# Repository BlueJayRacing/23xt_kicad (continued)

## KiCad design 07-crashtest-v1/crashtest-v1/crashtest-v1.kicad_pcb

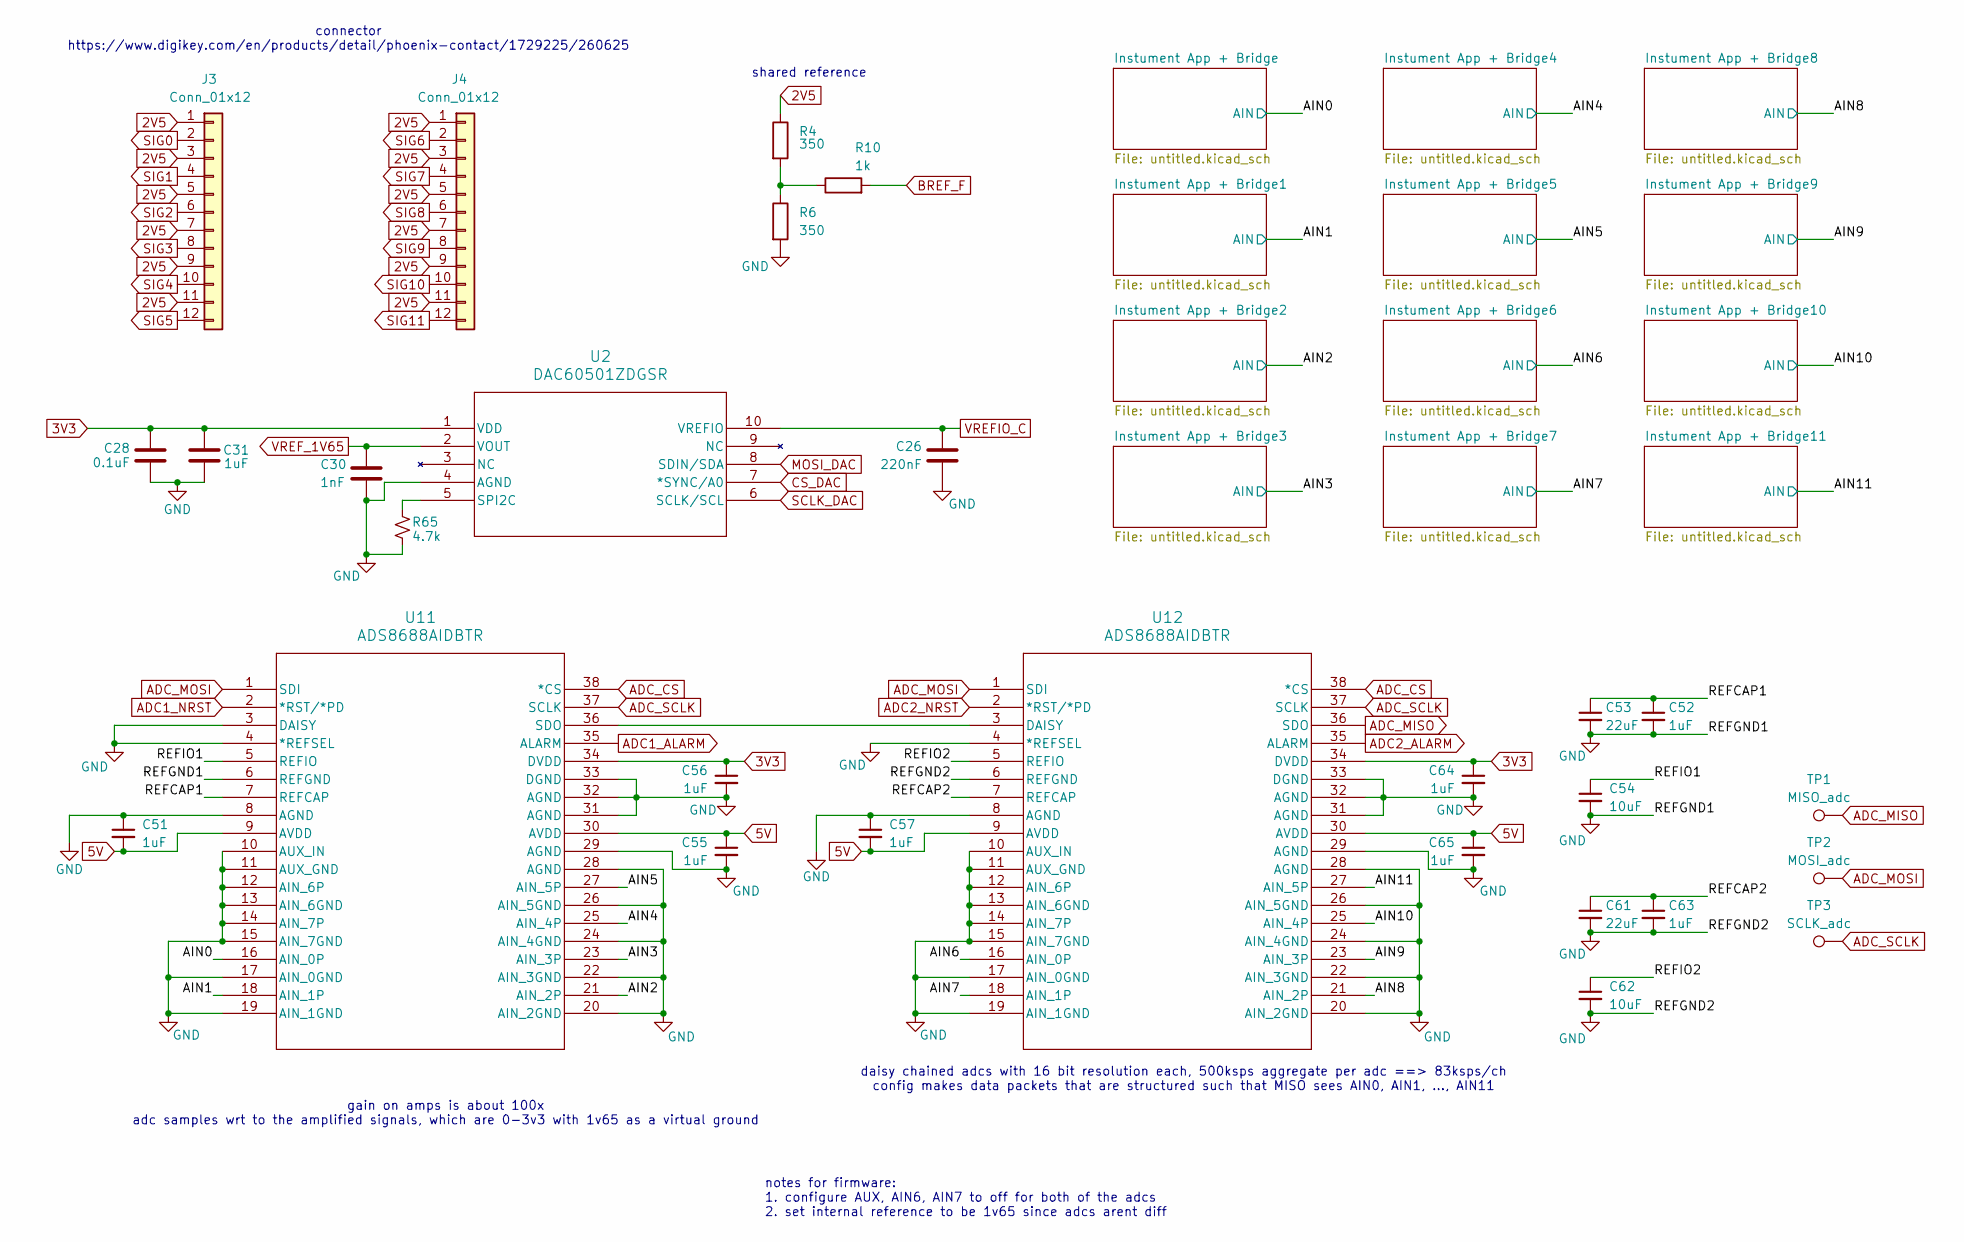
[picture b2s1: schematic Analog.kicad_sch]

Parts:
C26: 220nF; C_0603_1608Metric_Pad1.08x0.95mm_HandSolder
C28: 0.1uF; C_0603_1608Metric_Pad1.08x0.95mm_HandSolder
C30: 1nF; C_0603_1608Metric_Pad1.08x0.95mm_HandSolder
C31, C51, C52, C55, C56, C57, C63, C64, C65: 1uF; C_0603_1608Metric_Pad1.08x0.95mm_HandSolder
C53, C61: 22uF; C_0603_1608Metric_Pad1.08x0.95mm_HandSolder
C54, C62: 10uF; C_0603_1608Metric_Pad1.08x0.95mm_HandSolder
J3, J4: Conn_01x12; TerminalBlock_Phoenix_MKDS-1,5-12-5.08_1x12_P5.08mm_Horizon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
R4, R6: 350; R_0603_1608Metric_Pad0.98x0.95mm_HandSolder
R10: 1k; R_0603_1608Metric_Pad0.98x0.95mm_HandSolder
R65: 4.7k; R_0603_1608Metric_Pad0.98x0.95mm_HandSolder
TP1: MISO_adc; TestPoint_Pad_1.0x1.0mm
TP2: MOSI_adc; TestPoint_Pad_1.0x1.0mm
TP3: SCLK_adc; TestPoint_Pad_1.0x1.0mm
U2: DAC60501ZDGSR; MSOP-10_3x3mm_P0.5mm
U11, U12: ADS8688AIDBTR; DBT38_TEX-L

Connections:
2V5: J3.1, J3.3, J3.5, J3.7, J3.9, J3.11, J4.1, J4.3, J4.5, J4.7, J4.9, J4.11, R4.1; also elsewhere on the board
3V3: C28.1, C31.1, C56.1, C64.1, U2.1 (VDD), U11.34 (DVDD), U12.34 (DVDD); also elsewhere on the board
5V: C51.2, C55.1, C57.2, C65.1, U11.9 (AVDD), U11.30 (AVDD), U12.9 (AVDD), U12.30 (AVDD); also elsewhere on the board
/Analog/AIN0: U11.16 (AIN_0P); also elsewhere on the board
/Analog/AIN1: U11.18 (AIN_1P); also elsewhere on the board
/Analog/AIN2: U11.21 (AIN_2P); also elsewhere on the board
/Analog/AIN3: U11.23 (AIN_3P); also elsewhere on the board
/Analog/AIN4: U11.25 (AIN_4P); also elsewhere on the board
/Analog/AIN5: U11.27 (AIN_5P); also elsewhere on the board
/Analog/AIN6: U12.16 (AIN_0P); also elsewhere on the board
/Analog/AIN7: U12.18 (AIN_1P); also elsewhere on the board
/Analog/AIN8: U12.21 (AIN_2P); also elsewhere on the board
/Analog/AIN9: U12.23 (AIN_3P); also elsewhere on the board
/Analog/AIN10: U12.25 (AIN_4P); also elsewhere on the board
/Analog/AIN11: U12.27 (AIN_5P); also elsewhere on the board
/Analog/REFCAP1: C52.1, C53.1, U11.7 (REFCAP)
/Analog/REFCAP2: C61.1, C63.1, U12.7 (REFCAP)
/Analog/REFIO1: C54.1, U11.5 (REFIO)
/Analog/REFIO2: C62.1, U12.5 (REFIO)
ADC1_ALARM: U11.35 (ALARM); also elsewhere on the board
ADC1_NRST: U11.2 (*RST/*PD); also elsewhere on the board
ADC2_ALARM: U12.35 (ALARM); also elsewhere on the board
ADC2_NRST: U12.2 (*RST/*PD); also elsewhere on the board
ADC_CS: U11.38 (*CS), U12.38 (*CS); also elsewhere on the board
ADC_MISO: TP1.1 (1_1), U12.36 (SDO); also elsewhere on the board
ADC_MOSI: TP2.1 (1_1), U11.1 (SDI), U12.1 (SDI); also elsewhere on the board
ADC_SCLK: TP3.1 (1_1), U11.37 (SCLK), U12.37 (SCLK); also elsewhere on the board
BREF_F: R10.2; also elsewhere on the board
CS_DAC: U2.7 (*SYNC/A0); also elsewhere on the board
GND: C26.1, C28.2, C30.1, C31.2, C51.1, C52.2, C53.2, C54.2, C55.2, C56.2, C57.1, C61.2, C62.2, C63.2, C64.2, C65.2, R6.2, R65.2, U2.4 (AGND), U11.3 (DAISY), U11.4 (*REFSEL), U11.6 (REFGND), U11.8 (AGND), U11.10 (AUX_IN), U11.11 (AUX_GND), U11.12 (AIN_6P), U11.13 (AIN_6GND), U11.14 (AIN_7P), U11.15 (AIN_7GND), U11.17 (AIN_0GND), U11.19 (AIN_1GND), U11.20 (AIN_2GND), U11.22 (AIN_3GND), U11.24 (AIN_4GND), U11.26 (AIN_5GND), U11.28 (AGND), U11.29 (AGND), U11.31 (AGND), U11.32 (AGND), U11.33 (DGND), U12.4 (*REFSEL), U12.6 (REFGND), U12.8 (AGND), U12.10 (AUX_IN), U12.11 (AUX_GND), U12.12 (AIN_6P), U12.13 (AIN_6GND), U12.14 (AIN_7P), U12.15 (AIN_7GND), U12.17 (AIN_0GND), U12.19 (AIN_1GND), U12.20 (AIN_2GND), U12.22 (AIN_3GND), U12.24 (AIN_4GND), U12.26 (AIN_5GND), U12.28 (AGND), U12.29 (AGND), U12.31 (AGND), U12.32 (AGND), U12.33 (DGND); also elsewhere on the board
MOSI_DAC: U2.8 (SDIN/SDA); also elsewhere on the board
unnamed: R4.2, R6.1, R10.1
unnamed: R65.1, U2.5 (SPI2C)
unnamed: U11.36 (SDO), U12.3 (DAISY)
SCLK_DAC: U2.6 (SCLK/SCL); also elsewhere on the board
SIG0: J3.2; also elsewhere on the board
SIG1: J3.4
SIG2: J3.6
SIG3: J3.8
SIG4: J3.10
SIG5: J3.12
SIG6: J4.2
SIG7: J4.4
SIG8: J4.6
SIG9: J4.8
SIG10: J4.10
SIG11: J4.12
VREFIO_C: C26.2, U2.10 (VREFIO)
VREF_1V65: C30.2, U2.2 (VOUT); also elsewhere on the board

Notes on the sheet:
shared reference
connector https://www.digikey.com/en/products/detail/phoenix-contact/1729225/260625
notes for firmware: 1. configure AUX, AIN6, AIN7 to off for both of the adcs 2. set internal reference to be 1v65 since adcs arent diff
gain on amps is about 100x adc samples wrt to the amplified signals, which are 0-3v3 with 1v65 as a virtual ground
daisy chained adcs with 16 bit resolution each, 500ksps aggregate per adc ==> 83ksps/ch config makes data packets that are structured such that MISO sees AIN0, AIN1, ..., AIN11

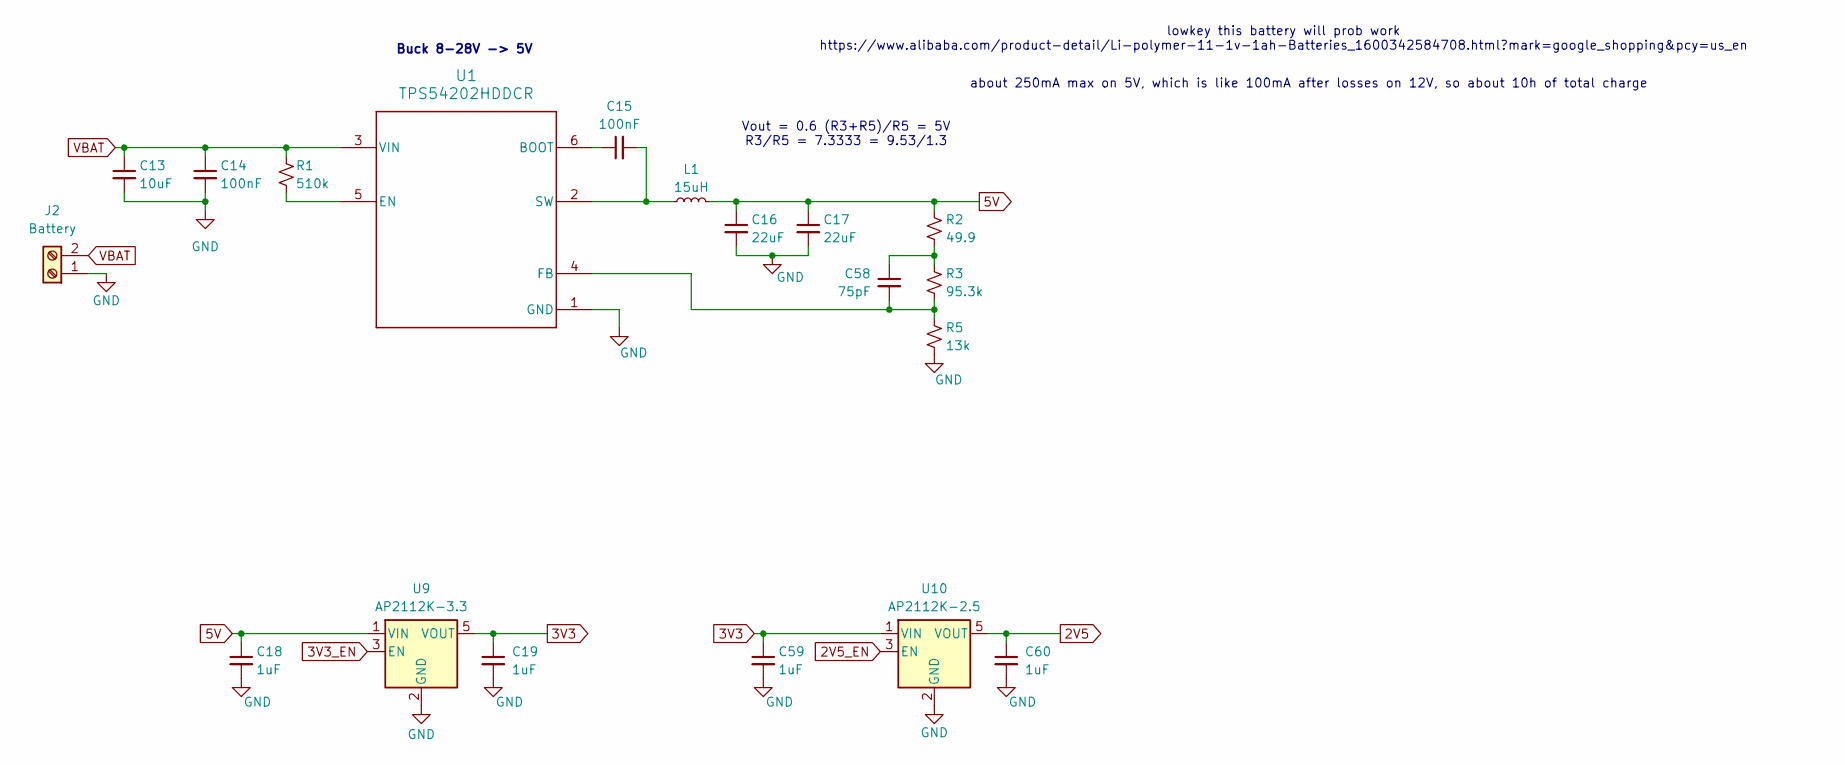
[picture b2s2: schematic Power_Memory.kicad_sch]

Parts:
C13: 10uF; C_0603_1608Metric_Pad1.08x0.95mm_HandSolder
C14, C15: 100nF; C_0603_1608Metric_Pad1.08x0.95mm_HandSolder
C16, C17: 22uF; C_0603_1608Metric_Pad1.08x0.95mm_HandSolder
C18, C19, C59, C60: 1uF; C_0603_1608Metric_Pad1.08x0.95mm_HandSolder
C58: 75pF; C_0603_1608Metric_Pad1.08x0.95mm_HandSolder
J2: Battery; TerminalBlock_Phoenix_MKDS-1,5-2-5.08_1x02_P5.08mm_Horizont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
L1: 15uH; L_0603_1608Metric_Pad1.05x0.95mm_HandSolder
R1: 510k; R_0603_1608Metric_Pad0.98x0.95mm_HandSolder
R2: 49.9; R_0603_1608Metric_Pad0.98x0.95mm_HandSolder
R3: 95.3k; R_0603_1608Metric_Pad0.98x0.95mm_HandSolder
R5: 13k; R_0603_1608Metric_Pad0.98x0.95mm_HandSolder
U1: TPS54202HDDCR; DDC0006A_L
U9: AP2112K-3.3; SOT-23-5
U10: AP2112K-2.5; SOT-23-5

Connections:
2V5: C60.1, U10.5 (VOUT); also elsewhere on the board
2V5_EN: U10.3 (EN); also elsewhere on the board
3V3: C19.1, C59.1, U9.5 (VOUT), U10.1 (VIN); also elsewhere on the board
3V3_EN: U9.3 (EN); also elsewhere on the board
5V: C16.1, C17.1, C18.1, L1.2, R2.1, U9.1 (VIN); also elsewhere on the board
GND: C13.2, C14.2, C16.2, C17.2, C18.2, C19.2, C59.2, C60.2, J2.1, R5.2, U1.1 (GND), U9.2 (GND), U10.2 (GND); also elsewhere on the board
unnamed: C58.1, R2.2, R3.1
unnamed: C15.1, U1.6 (BOOT)
unnamed: R1.2, U1.5 (EN)
unnamed: C58.2, R3.2, R5.1, U1.4 (FB)
unnamed: C15.2, L1.1, U1.2 (SW)
VBAT: C13.1, C14.1, J2.2, R1.1, U1.3 (VIN)

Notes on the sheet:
lowkey this battery will prob work https://www.alibaba.com/product-detail/Li-polymer-11-1v-1ah-Batteries_1600342584708.html?mark=google_shopping&pcy=us_en
about 250mA max on 5V, which is like 100mA after losses on 12V, so about 10h of total charge
Buck 8-28V -> 5V
Vout = 0.6 (R3+R5)/R5 = 5V R3/R5 = 7.3333 = 9.53/1.3

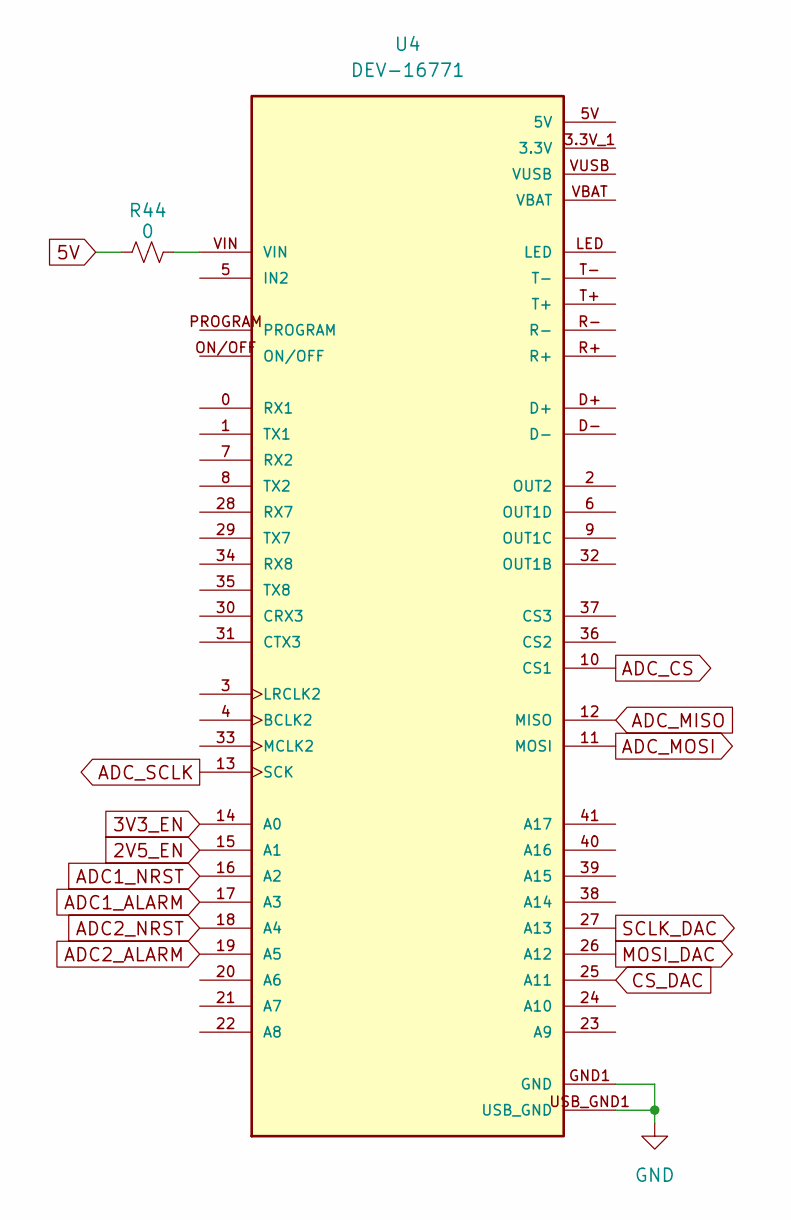
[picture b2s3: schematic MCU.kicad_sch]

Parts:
R44: 0; R_0603_1608Metric_Pad0.98x0.95mm_HandSolder
U4: DEV-16771; MODULE_DEV-16771; PARTREV 4.1

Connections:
2V5_EN: U4.15 (A1); also elsewhere on the board
3.3V: U4.3.3V_1 (3.3V), U4.3.3V_2 (3.3V), U4.3.3V_3 (3.3V)
3V3_EN: U4.14 (A0); also elsewhere on the board
5V: R44.1; also elsewhere on the board
ADC1_ALARM: U4.17 (A3); also elsewhere on the board
ADC1_NRST: U4.16 (A2); also elsewhere on the board
ADC2_ALARM: U4.19 (A5); also elsewhere on the board
ADC2_NRST: U4.18 (A4); also elsewhere on the board
ADC_CS: U4.10 (CS1); also elsewhere on the board
ADC_MISO: U4.12 (MISO); also elsewhere on the board
ADC_MOSI: U4.11 (MOSI); also elsewhere on the board
ADC_SCLK: U4.13 (SCK); also elsewhere on the board
CS_DAC: U4.25 (A11); also elsewhere on the board
GND: U4.GND1 (GND), U4.GND2 (GND), U4.GND3 (GND), U4.GND4 (GND), U4.GND5 (GND), U4.USB_GND1 (USB_GND), U4.USB_GND2 (USB_GND); also elsewhere on the board
MOSI_DAC: U4.26 (A12); also elsewhere on the board
unnamed: R44.2, U4.VIN
SCLK_DAC: U4.27 (A13); also elsewhere on the board

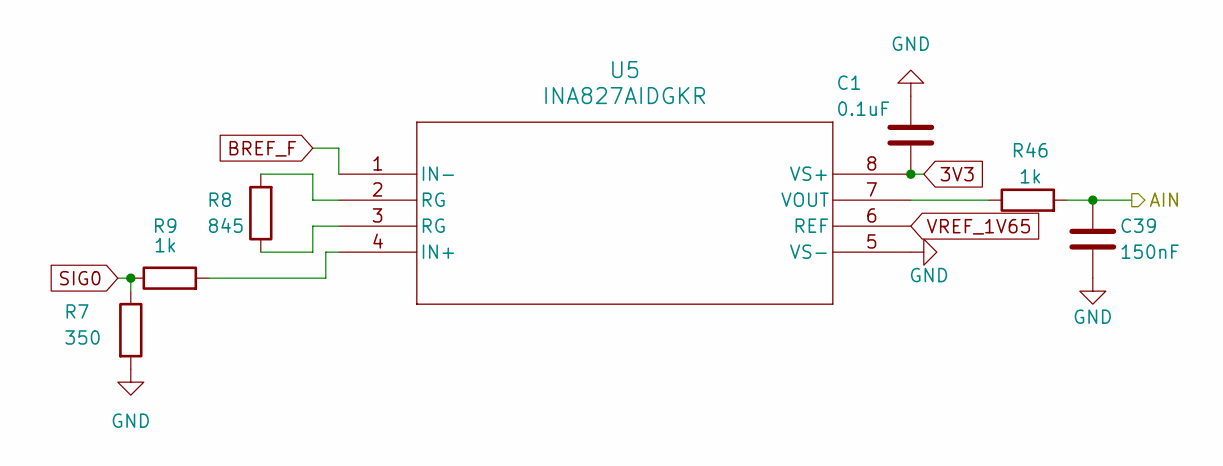
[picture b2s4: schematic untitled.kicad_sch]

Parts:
C1: 0.1uF; C_0603_1608Metric_Pad1.08x0.95mm_HandSolder
C39: 150nF; C_0603_1608Metric_Pad1.08x0.95mm_HandSolder
R7: 350; R_0603_1608Metric_Pad0.98x0.95mm_HandSolder
R8: 845; R_0603_1608Metric_Pad0.98x0.95mm_HandSolder
R9, R46: 1k; R_0603_1608Metric_Pad0.98x0.95mm_HandSolder
U5: INA827AIDGKR; VSSOP-8_3x3mm_P0.65mm

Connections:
3V3: C1.1, U5.8 (VS+); also elsewhere on the board
/Analog/AIN0: C39.2, R46.2; also elsewhere on the board
BREF_F: U5.1 (IN-); also elsewhere on the board
GND: C1.2, C39.1, R7.2, U5.5 (VS-); also elsewhere on the board
unnamed: R8.1, U5.3 (RG)
unnamed: R8.2, U5.2 (RG)
unnamed: R9.2, U5.4 (IN+)
unnamed: R46.1, U5.7 (VOUT)
SIG0: R7.1, R9.1; also elsewhere on the board
VREF_1V65: U5.6 (REF); also elsewhere on the board

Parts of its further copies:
C2, C3, C4, C5, C6, C7, C8, C9, C10, C11, C12: 0.1uF; C_0603_1608Metric_Pad1.08x0.95mm_HandSolder
C40, C41, C42, C43, C44, C45, C46, C47, C48, C49, C50: 150nF; C_0603_1608Metric_Pad1.08x0.95mm_HandSolder
R11, R14, R17, R20, R23, R26, R29, R32, R35, R38, R41: 350; R_0603_1608Metric_Pad0.98x0.95mm_HandSolder
R12, R15, R18, R21, R24, R27, R30, R33, R36, R39, R42, R47, R48, R49, R50, R51, R52, R53, R54, R55, R56, R57: 1k; R_0603_1608Metric_Pad0.98x0.95mm_HandSolder
R13, R16, R19, R22, R25, R28, R31, R34, R37, R40, R43: 845; R_0603_1608Metric_Pad0.98x0.95mm_HandSolder
U6, U7, U8, U14, U15, U16, U17, U18, U19, U20, U21: INA827AIDGKR; VSSOP-8_3x3mm_P0.65mm

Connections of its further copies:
3V3: C2.1, C3.1, C4.1, C5.1, C6.1, C7.1, C8.1, C9.1, C10.1, C11.1, C12.1, U6.8 (VS+), U7.8 (VS+), U8.8 (VS+), U14.8 (VS+), U15.8 (VS+), U16.8 (VS+), U17.8 (VS+), U18.8 (VS+), U19.8 (VS+), U20.8 (VS+), U21.8 (VS+); also elsewhere on the board
/Analog/AIN1: C40.2, R47.2; also elsewhere on the board
/Analog/AIN2: C41.2, R48.2; also elsewhere on the board
/Analog/AIN3: C42.2, R49.2; also elsewhere on the board
/Analog/AIN4: C43.2, R50.2; also elsewhere on the board
/Analog/AIN5: C44.2, R51.2; also elsewhere on the board
/Analog/AIN6: C45.2, R52.2; also elsewhere on the board
/Analog/AIN7: C46.2, R53.2; also elsewhere on the board
/Analog/AIN8: C47.2, R54.2; also elsewhere on the board
/Analog/AIN9: C48.2, R55.2; also elsewhere on the board
/Analog/AIN10: C49.2, R56.2; also elsewhere on the board
/Analog/AIN11: C50.2, R57.2; also elsewhere on the board
BREF_F: U6.1 (IN-), U7.1 (IN-), U8.1 (IN-), U14.1 (IN-), U15.1 (IN-), U16.1 (IN-), U17.1 (IN-), U18.1 (IN-), U19.1 (IN-), U20.1 (IN-), U21.1 (IN-); also elsewhere on the board
GND: C2.2, C3.2, C4.2, C5.2, C6.2, C7.2, C8.2, C9.2, C10.2, C11.2, C12.2, C40.1, C41.1, C42.1, C43.1, C44.1, C45.1, C46.1, C47.1, C48.1, C49.1, C50.1, R11.2, R14.2, R17.2, R20.2, R23.2, R26.2, R29.2, R32.2, R35.2, R38.2, R41.2, U6.5 (VS-), U7.5 (VS-), U8.5 (VS-), U14.5 (VS-), U15.5 (VS-), U16.5 (VS-), U17.5 (VS-), U18.5 (VS-), U19.5 (VS-), U20.5 (VS-), U21.5 (VS-); also elsewhere on the board
unnamed: R13.1, U6.3 (RG)
unnamed: R13.2, U6.2 (RG)
unnamed: R16.1, U7.3 (RG)
unnamed: R16.2, U7.2 (RG)
unnamed: R19.1, U8.3 (RG)
unnamed: R19.2, U8.2 (RG)
unnamed: R22.1, U14.3 (RG)
unnamed: R22.2, U14.2 (RG)
unnamed: R25.1, U15.3 (RG)
unnamed: R25.2, U15.2 (RG)
unnamed: R28.1, U16.3 (RG)
unnamed: R28.2, U16.2 (RG)
unnamed: R31.1, U17.3 (RG)
unnamed: R31.2, U17.2 (RG)
unnamed: R34.1, U18.3 (RG)
unnamed: R34.2, U18.2 (RG)
unnamed: R37.1, U19.3 (RG)
unnamed: R37.2, U19.2 (RG)
unnamed: R40.1, U20.3 (RG)
unnamed: R40.2, U20.2 (RG)
unnamed: R43.1, U21.3 (RG)
unnamed: R43.2, U21.2 (RG)
unnamed: R12.2, U6.4 (IN+)
unnamed: R47.1, U6.7 (VOUT)
unnamed: R15.2, U7.4 (IN+)
unnamed: R48.1, U7.7 (VOUT)
unnamed: R18.2, U8.4 (IN+)
unnamed: R49.1, U8.7 (VOUT)
unnamed: R21.2, U14.4 (IN+)
unnamed: R50.1, U14.7 (VOUT)
unnamed: R24.2, U15.4 (IN+)
unnamed: R51.1, U15.7 (VOUT)
unnamed: R27.2, U16.4 (IN+)
unnamed: R52.1, U16.7 (VOUT)
unnamed: R30.2, U17.4 (IN+)
unnamed: R53.1, U17.7 (VOUT)
unnamed: R33.2, U18.4 (IN+)
unnamed: R54.1, U18.7 (VOUT)
unnamed: R36.2, U19.4 (IN+)
unnamed: R55.1, U19.7 (VOUT)
unnamed: R39.2, U20.4 (IN+)
unnamed: R56.1, U20.7 (VOUT)
unnamed: R42.2, U21.4 (IN+)
unnamed: R57.1, U21.7 (VOUT)
SIG0: R11.1, R12.1, R14.1, R15.1, R17.1, R18.1, R20.1, R21.1, R23.1, R24.1, R26.1, R27.1, R29.1, R30.1, R32.1, R33.1, R35.1, R36.1, R38.1, R39.1, R41.1, R42.1; also elsewhere on the board
VREF_1V65: U6.6 (REF), U7.6 (REF), U8.6 (REF), U14.6 (REF), U15.6 (REF), U16.6 (REF), U17.6 (REF), U18.6 (REF), U19.6 (REF), U20.6 (REF), U21.6 (REF); also elsewhere on the board

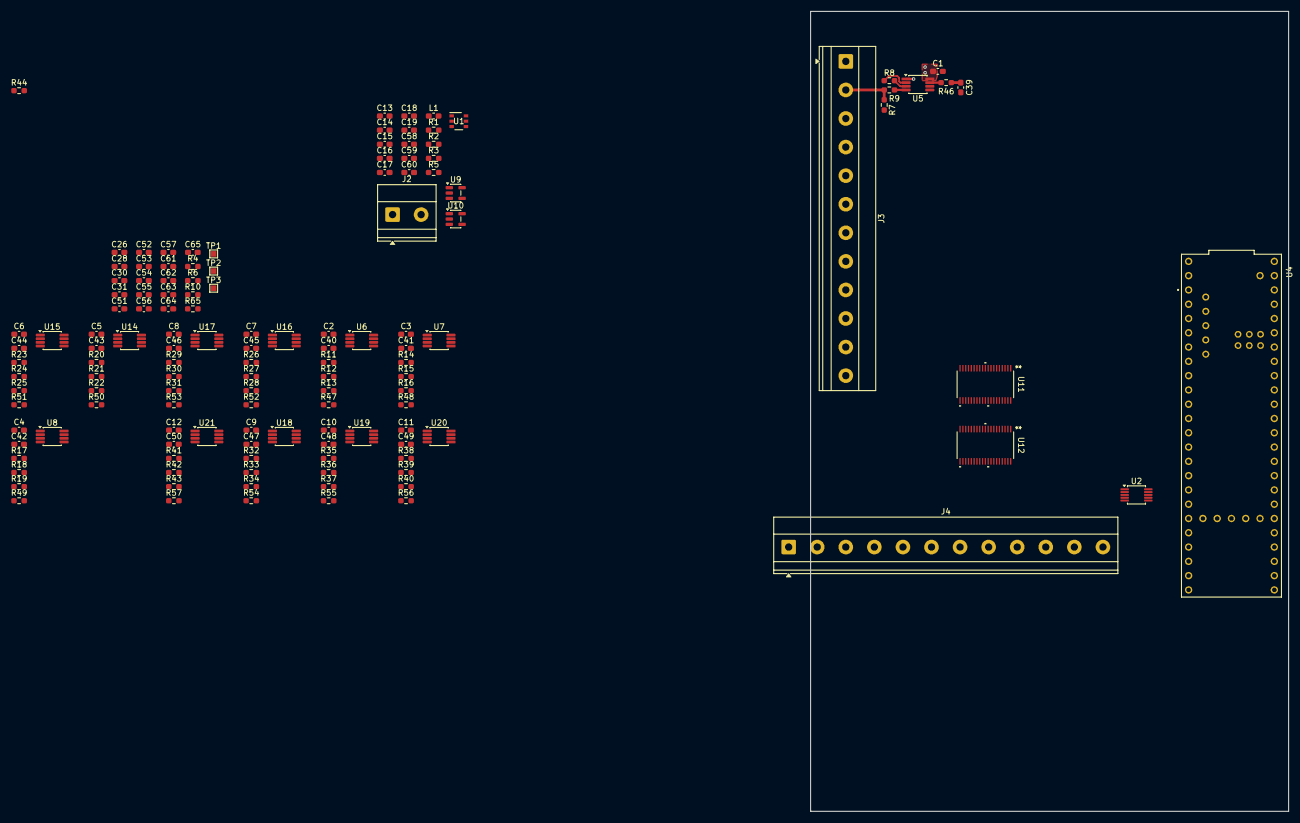
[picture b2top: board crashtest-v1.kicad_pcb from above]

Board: 4 copper layers, 85.0 x 142.2 mm, 133 parts (0 on the bottom side), 96 nets.

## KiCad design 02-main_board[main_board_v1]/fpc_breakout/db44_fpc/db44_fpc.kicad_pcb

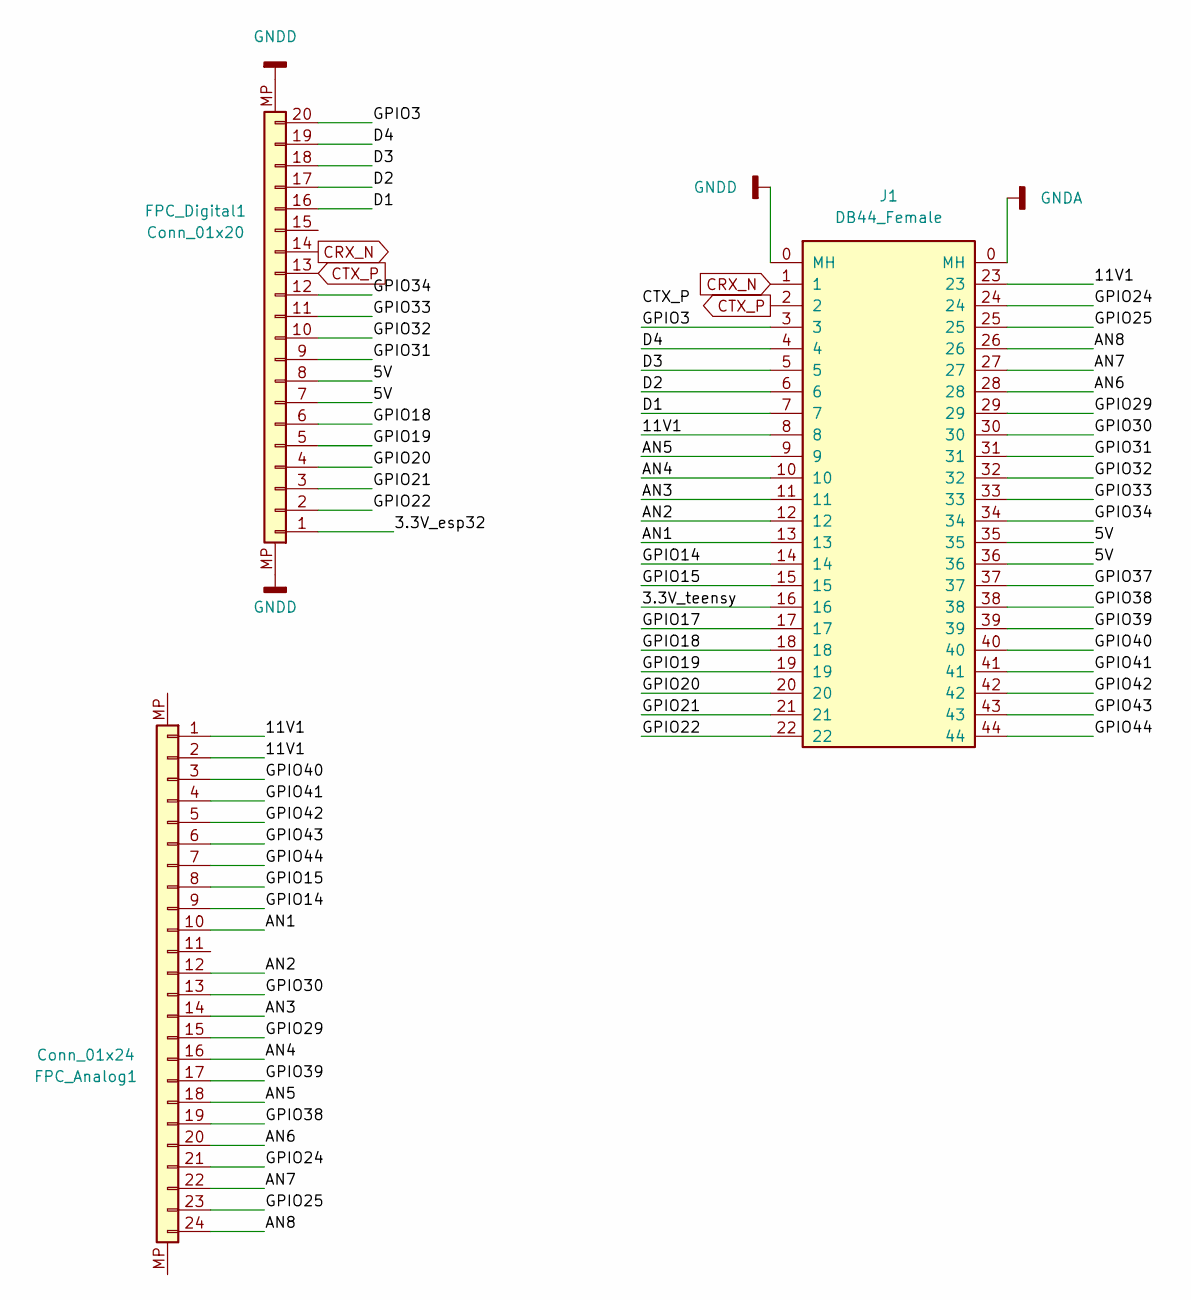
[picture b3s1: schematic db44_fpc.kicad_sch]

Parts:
FPC_Analog1: Conn_01x24; TE_2-84953-4_1x24-1MP_P1.0mm_Horizontal
FPC_Digital1: Conn_01x20; TE_2-84953-0_1x20-1MP_P1.0mm_Horizontal
J1: DB44_Female; DSUB-44-HD_Socket_Vertical_P2.29x1.98mm_MountingHoles

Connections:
/3.3V_esp32: FPC_Digital1.1
/3.3V_teensy: J1.16
/5V: FPC_Digital1.7, FPC_Digital1.8, J1.35, J1.36
/11V1: FPC_Analog1.1, FPC_Analog1.2, J1.8, J1.23
/AN1: FPC_Analog1.10, J1.13
/AN2: FPC_Analog1.12, J1.12
/AN3: FPC_Analog1.14, J1.11
/AN4: FPC_Analog1.16, J1.10
/AN5: FPC_Analog1.18, J1.9
/AN6: FPC_Analog1.20, J1.28
/AN7: FPC_Analog1.22, J1.27
/AN8: FPC_Analog1.24, J1.26
/D1: FPC_Digital1.16, J1.7
/D2: FPC_Digital1.17, J1.6
/D3: FPC_Digital1.18, J1.5
/D4: FPC_Digital1.19, J1.4
/GPIO3: FPC_Digital1.20, J1.3
/GPIO14: FPC_Analog1.9, J1.14
/GPIO15: FPC_Analog1.8, J1.15
/GPIO17: J1.17
/GPIO18: FPC_Digital1.6, J1.18
/GPIO19: FPC_Digital1.5, J1.19
/GPIO20: FPC_Digital1.4, J1.20
/GPIO21: FPC_Digital1.3, J1.21
/GPIO22: FPC_Digital1.2, J1.22
/GPIO24: FPC_Analog1.21, J1.24
/GPIO25: FPC_Analog1.23, J1.25
/GPIO29: FPC_Analog1.15, J1.29
/GPIO30: FPC_Analog1.13, J1.30
/GPIO31: FPC_Digital1.9, J1.31
/GPIO32: FPC_Digital1.10, J1.32
/GPIO33: FPC_Digital1.11, J1.33
/GPIO34: FPC_Digital1.12, J1.34
/GPIO37: J1.37
/GPIO38: FPC_Analog1.19, J1.38
/GPIO39: FPC_Analog1.17, J1.39
/GPIO40: FPC_Analog1.3, J1.40
/GPIO41: FPC_Analog1.4, J1.41
/GPIO42: FPC_Analog1.5, J1.42
/GPIO43: FPC_Analog1.6, J1.43
/GPIO44: FPC_Analog1.7, J1.44
CRX_N: FPC_Digital1.14, J1.1
CTX_P: FPC_Digital1.13, J1.2
GNDD: FPC_Digital1.MP, J1.0 (MH)

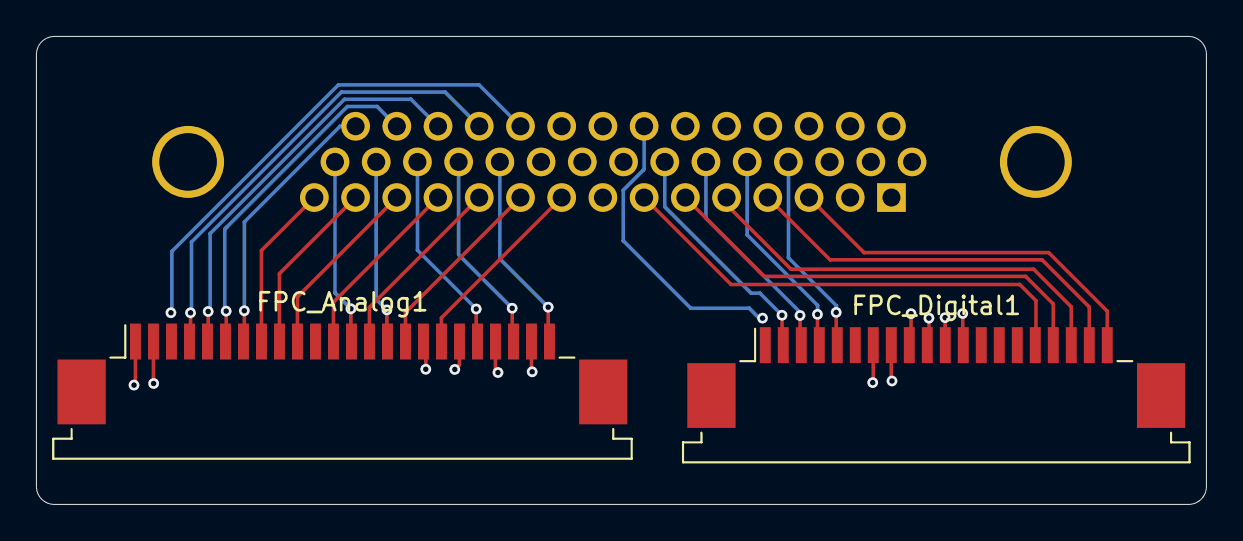
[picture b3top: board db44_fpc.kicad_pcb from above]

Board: 4 copper layers, 65.0 x 26.0 mm, 3 parts (1 on the bottom side), 39 nets.

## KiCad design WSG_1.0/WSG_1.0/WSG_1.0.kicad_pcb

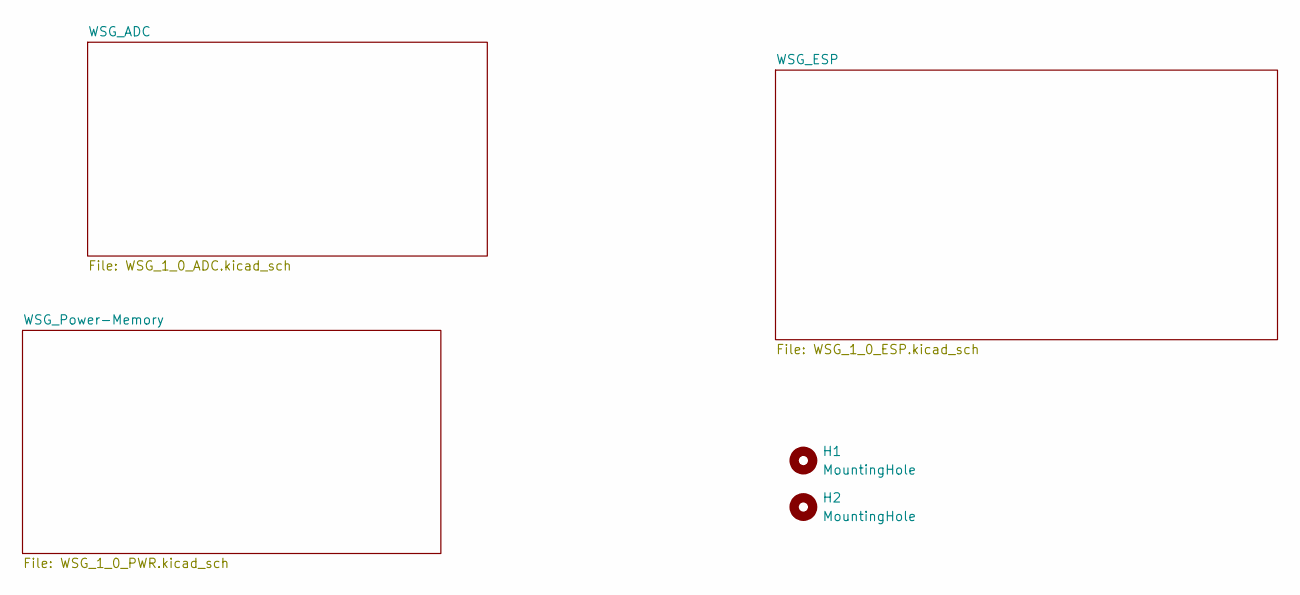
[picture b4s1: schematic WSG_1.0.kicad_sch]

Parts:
H1, H2: MountingHole; MountingHole_3.2mm_M3
